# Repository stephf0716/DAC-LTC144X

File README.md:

# DAC-LTC144X

A small KiCad breakout board and an Arduino driver for the **Linear Technology
LTC1446 / LTC1446L** — a dual 12-bit rail-to-rail DAC with an internal
reference and a 3-wire SPI interface in an 8-pin package.

<!-- Board render and schematic images go in docs/ and get embedded here. -->

## The part

| | LTC1446 | LTC1446L |
|---|---|---|
| Supply | 4.5V – 5.5V | 2.7V – 5.5V |
| Full-scale output | 4.095V (1mV per LSB) | 2.5V |
| Resolution | 12 bits, 2 channels | 12 bits, 2 channels |
| Interface | 3-wire SPI, 24-bit word | 3-wire SPI, 24-bit word |
| Settling time | 14µs to ±0.5 LSB | 14µs to ±0.5 LSB |

Both channels are written in a single 24-bit transfer: the first 12 bits set
DAC A, the second 12 set DAC B. Data is latched on the **rising** edge of CLK
(SPI mode 0, MSB first), and the outputs update when CS/LD returns high. The
DAC has a power-on reset that clears both channels to 0V.

## The board

Two-layer, 18 × 22 mm, through-hole headers, designed in KiCad 6.

| Ref | Value | Purpose |
|---|---|---|
| U1 | LTC1446 | Dual 12-bit DAC, SO-8 |
| R1 | 10k | Pull-up on CS/LD to VCC |
| C1 | 0.1µF | VCC bypass |
| J1 | 1x5 header | Control in — CLK, D_IN, CS, VCC, GND |
| J2 | 1x2 header | Analog out — Vout A, Vout B |

Open `LTC1446-BRD.kicad_pro` in KiCad 6 or newer.

### Wiring

| J1 pin | Signal | Arduino (Uno) |
|---|---|---|
| 1 | CLK | 13 (SCK) |
| 2 | D_IN | 11 (MOSI) |
| 3 | CS | 10 (or any digital pin) |
| 4 | VCC | 5V |
| 5 | GND | GND |

The DAC's D_OUT pin is brought to U1 only; it exists so multiple LTC1446s can
be daisy-chained, and is left unconnected on this board.

## The Arduino library

Copy this repository into your Arduino `libraries/` folder, or clone it there:

```bash
git clone https://github.com/stephf0716/DAC-LTC144X ~/Documents/Arduino/libraries/LTC1446
```

```cpp
#include <LTC1446.h>

LTC1446 dac(10);  // CS/LD wired to pin 10

void setup() {
  dac.begin();
  dac.setVoltage(2048, 0);  // A to mid-scale (~2.048V), B to 0V
}

void loop() {}
```

### API

- `LTC1446(uint8_t csPin)` — construct with the pin wired to CS/LD.
- `begin()` — configures the CS pin and starts SPI.
- `setVoltage(uint16_t voutA, uint16_t voutB)` — writes both channels in one
  transfer. Codes run `0` to `LTC1446_MAX_CODE` (4095) and are clamped, since
  a value wider than 12 bits would overflow into the other channel.

See [examples/BasicSweep](examples/BasicSweep/BasicSweep.ino) for a full sketch
that ramps both channels.

## Repository layout

```
src/                    Arduino library sources
examples/BasicSweep/    example sketch
datasheets/             LTC1446 datasheet
LTC1446-BRD.*           KiCad 6 project, schematic, and PCB layout
```

## License

MIT — see [LICENSE](LICENSE). The bundled datasheet is the property of Linear
Technology / Analog Devices and is included for convenience only.

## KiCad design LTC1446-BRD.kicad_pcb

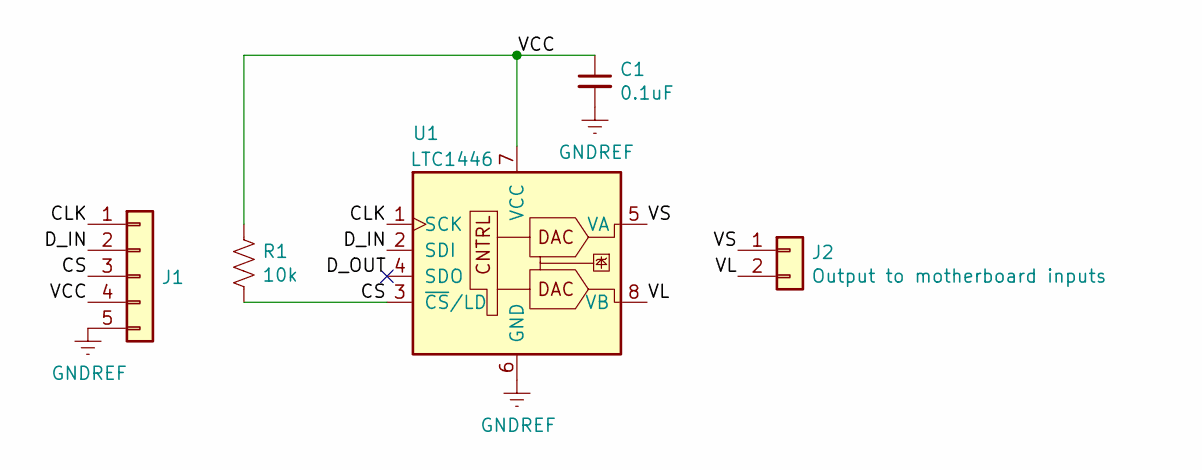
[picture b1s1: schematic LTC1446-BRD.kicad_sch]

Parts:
C1: 0.1uF; C_0805_2012Metric_Pad1.15x1.40mm_HandSolder
J1: Conn_01x05; PinSocket_1x05_P2.54mm_Vertical
J2: Output to motherboard inputs; PinSocket_1x02_P2.54mm_Vertical
R1: 10k; R_Axial_DIN0207_L6.3mm_D2.5mm_P10.16mm_Horizontal
U1: LTC1446; DIP-8_W7.62mm_Socket

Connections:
/CLK: J1.1, U1.1 (SCK)
/CS: J1.3, R1.2, U1.3 (~CS/LD)
/D_IN: J1.2, U1.2 (SDI)
/D_OUT: U1.4 (SDO)
/VCC: C1.1, J1.4, R1.1, U1.7 (VCC)
/VL: J2.2, U1.8 (VB)
/VS: J2.1, U1.5 (VA)
GNDREF: C1.2, J1.5, U1.6 (GND)

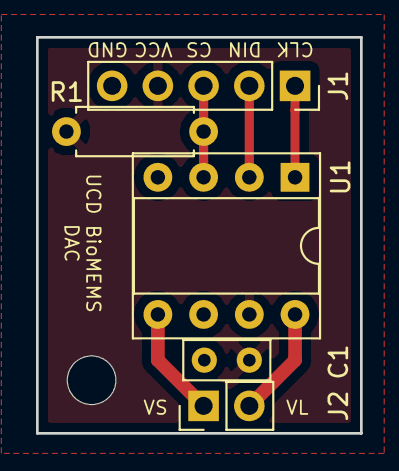
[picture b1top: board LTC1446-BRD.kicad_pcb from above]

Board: 2 copper layers, 18.0 x 22.0 mm, 5 parts (0 on the bottom side), 7 nets.

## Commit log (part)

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2018-07-12 added the Arduino lib
2018-07-31 Finished LTC1446 board
2018-08-03 PCB adjustments
    * added pull-up on CS
    * added a mounting hole
2022-03-17 Create LICENSE
2022-03-21 project structure update
    * deleted unused datasheet
    * updated to latest kicad version
